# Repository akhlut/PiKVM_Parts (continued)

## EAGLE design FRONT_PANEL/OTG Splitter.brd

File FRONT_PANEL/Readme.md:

Front Panel splitters to allow ATX control

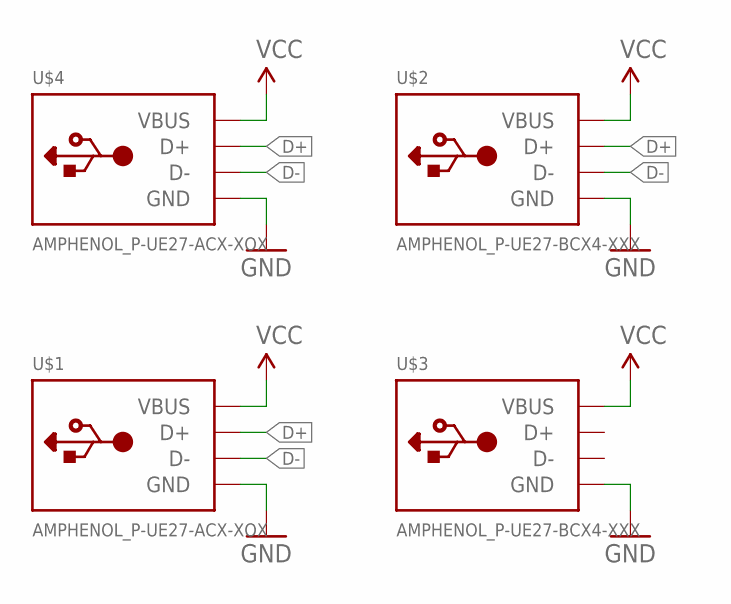
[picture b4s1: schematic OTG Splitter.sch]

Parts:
U$1, U$4: AMPHENOL_P-UE27-ACX-XOX; USBA_AMPHENOL-UE27-RA
U$2, U$3: AMPHENOL_P-UE27-BCX4-XXX; USBB_AMPHENOL-UE27-BC

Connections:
D+: U$1.P$3 (D+), U$2.P$3 (D+), U$4.P$3 (D+)
D-: U$1.P$2 (D-), U$2.P$2 (D-), U$4.P$2 (D-)
GND: U$1.P$4 (GND), U$2.P$4 (GND), U$3.P$4 (GND), U$4.P$4 (GND)
VCC: U$1.P$1 (VBUS), U$2.P$1 (VBUS), U$3.P$1 (VBUS), U$4.P$1 (VBUS)

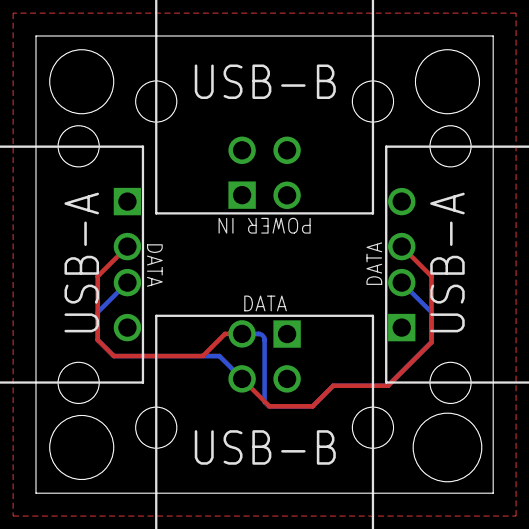
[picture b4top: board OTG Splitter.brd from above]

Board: 2 copper layers, 25.4 x 25.4 mm, 4 parts (0 on the bottom side), 4 nets.

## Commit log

2020-09-16 Rename ATX.md to Readme.md
2020-09-16 Rename USB_POWER_SPLITTER/Readme.md to OTG_SPLITTER/Readme.md
